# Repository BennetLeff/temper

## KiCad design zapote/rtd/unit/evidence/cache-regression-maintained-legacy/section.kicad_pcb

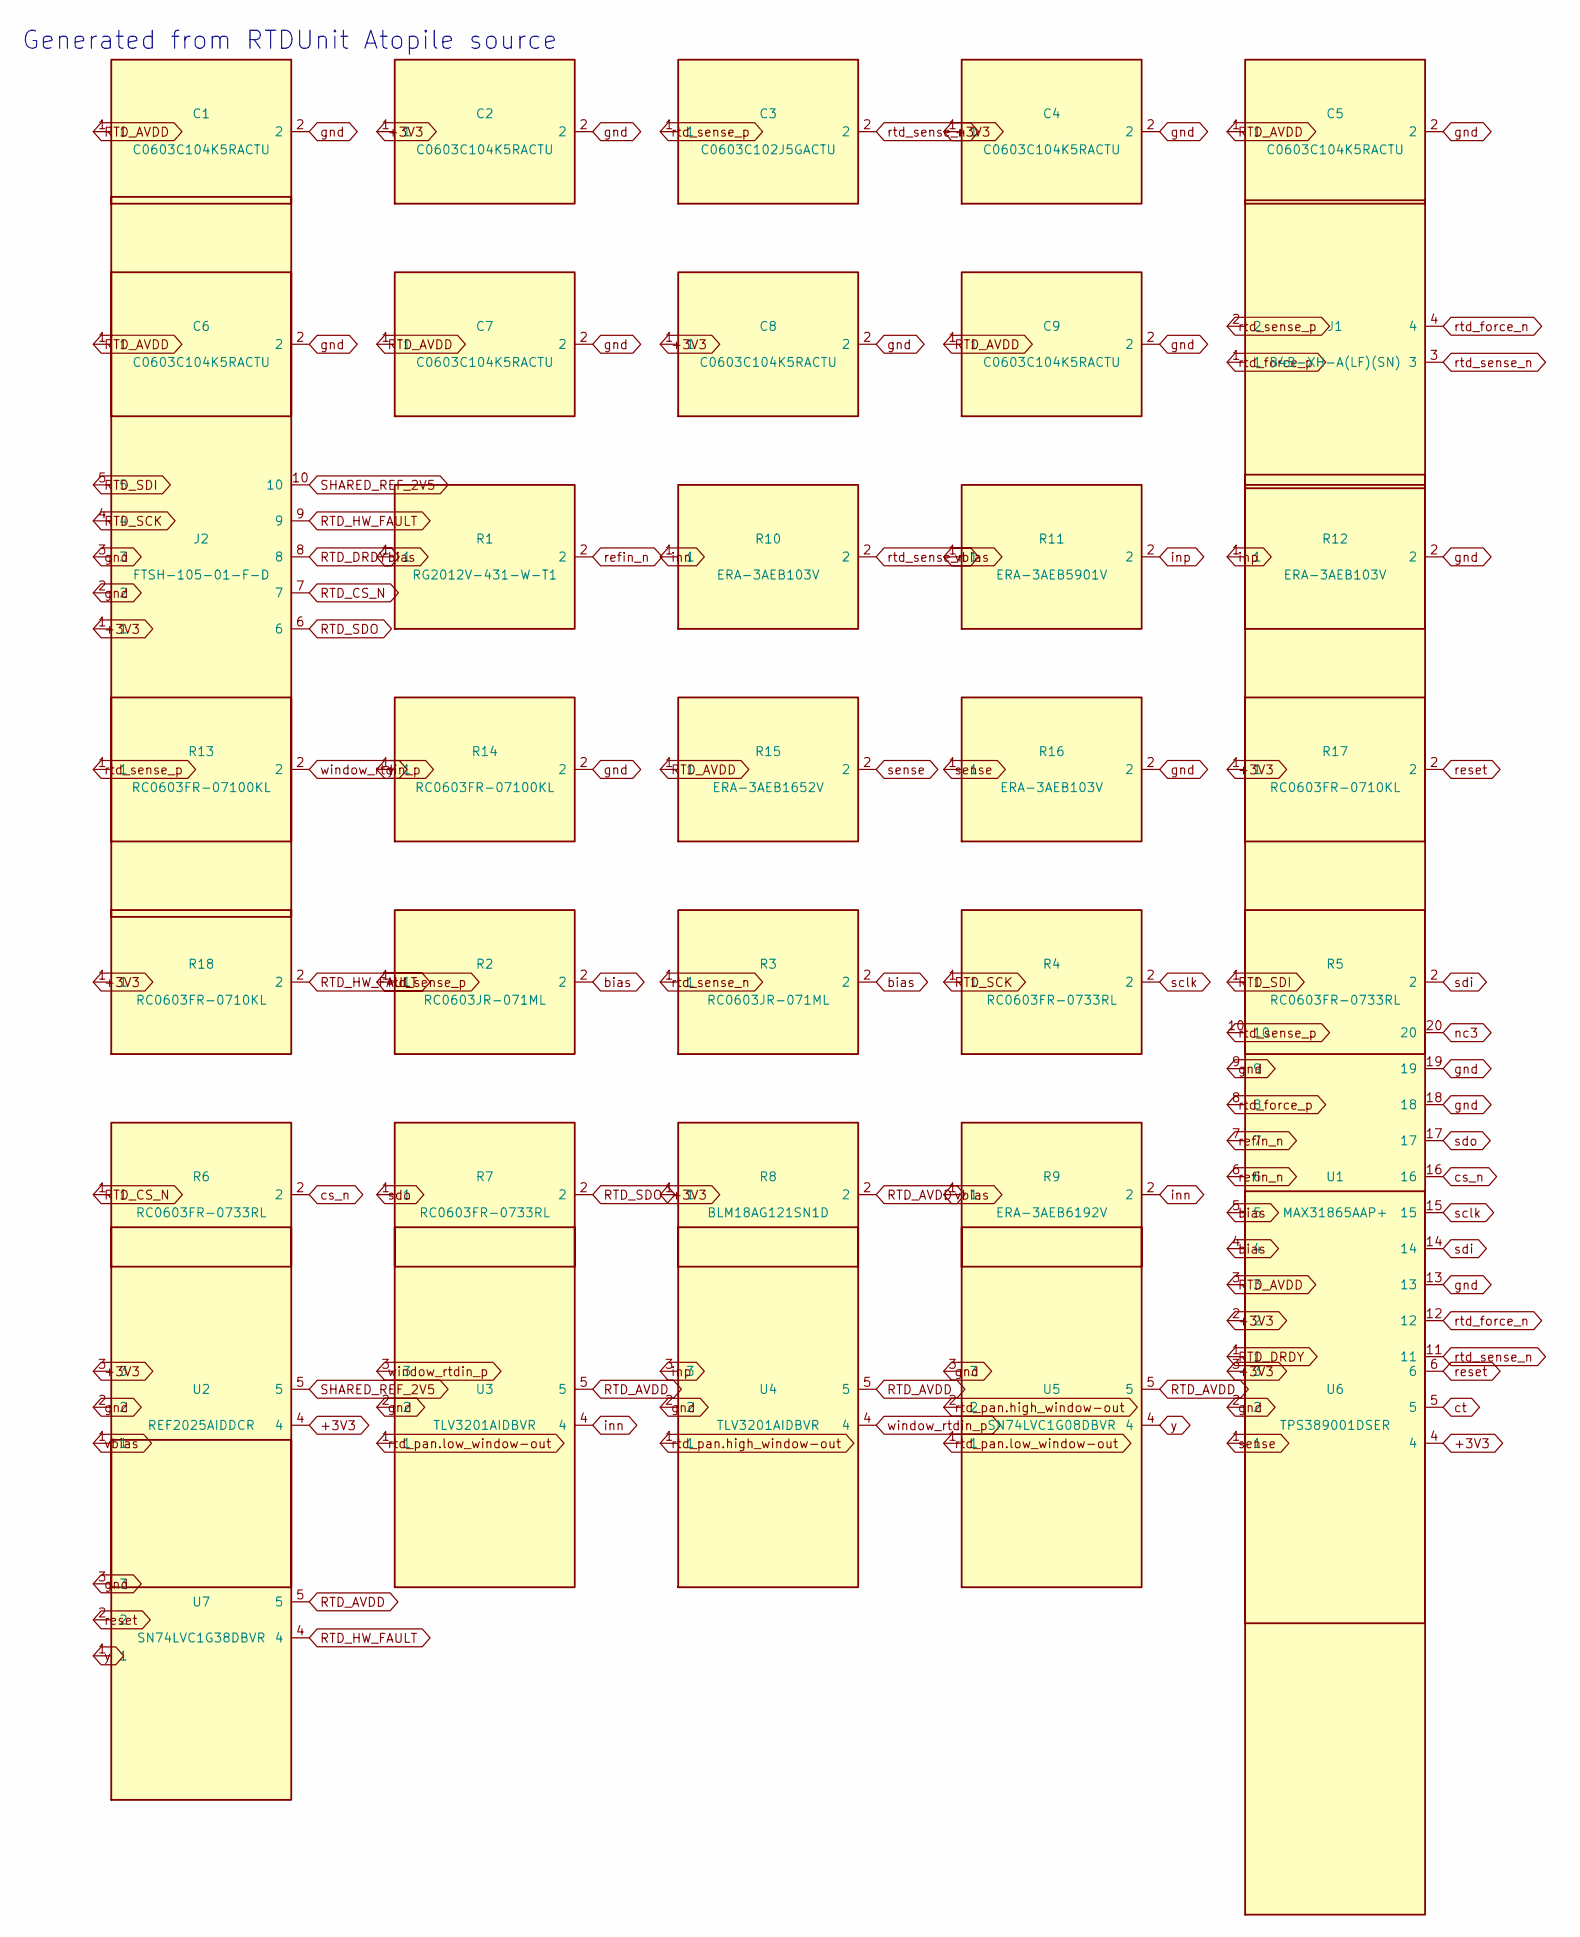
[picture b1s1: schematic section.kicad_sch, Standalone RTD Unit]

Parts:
C1, C2, C4, C5, C6, C7, C8, C9: C0603C104K5RACTU; C_0603_1608Metric
C3: C0603C102J5GACTU; C_0603_1608Metric
J1: B4B-XH-A(LF)(SN); JST_XH_B4B-XH-A_1x04_P2.50mm_Vertical
J2: FTSH-105-01-F-D; FTSH-105-01-F-D_2x5_P1.27mm
R1: RG2012V-431-W-T1; R_0805_2012Metric
R2, R3: RC0603JR-071ML; R_0603_1608Metric
R4, R5, R6, R7: RC0603FR-0733RL; R_0603_1608Metric
R8: BLM18AG121SN1D; L_0603_1608Metric
R9: ERA-3AEB6192V; R_0603_1608Metric
R10, R12, R16: ERA-3AEB103V; R_0603_1608Metric
R11: ERA-3AEB5901V; R_0603_1608Metric
R13, R14: RC0603FR-07100KL; R_0603_1608Metric
R15: ERA-3AEB1652V; R_0603_1608Metric
R17, R18: RC0603FR-0710KL; R_0603_1608Metric
U1: MAX31865AAP+; SSOP-20_3.9x8.7mm_P0.635mm
U2: REF2025AIDDCR; SOT-23-5
U3, U4: TLV3201AIDBVR; SOT-23-5
U5: SN74LVC1G08DBVR; SOT-23-5
U6: TPS389001DSER; TPS389001DSER_WSON-6_DSE
U7: SN74LVC1G38DBVR; SOT-23-5

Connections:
+3V3: C2.1, C4.1, C8.1, J2.1, R8.1, R17.1, R18.1, U1.2, U2.3, U2.4, U6.3, U6.4
RTD_AVDD: C1.1, C5.1, C6.1, C7.1, C9.1, R8.2, R15.1, U1.3, U3.5, U4.5, U5.5, U7.5
RTD_CS_N: J2.7, R6.1
RTD_DRDY: J2.8, U1.1
RTD_HW_FAULT: J2.9, R18.2, U7.4
RTD_SCK: J2.4, R4.1
RTD_SDI: J2.5, R5.1
RTD_SDO: J2.6, R7.2
SHARED_REF_2V5: J2.10, U2.5
bias: R1.1, R2.2, R3.2, U1.4, U1.5
cs_n: R6.2, U1.16
ct: U6.5
gnd: C1.2, C2.2, C4.2, C5.2, C6.2, C7.2, C8.2, C9.2, J2.2, J2.3, R12.2, R14.2, R16.2, U1.9, U1.13, U1.18, U1.19, U2.2, U3.2, U4.2, U5.3, U6.2, U7.3
inn: R9.2, R10.1, U3.4
inp: R11.2, R12.1, U4.3
nc3: U1.20
refin_n: R1.2, U1.6, U1.7
reset: R17.2, U6.6, U7.2
rtd_force_n: J1.4, U1.12
rtd_force_p: J1.1, U1.8
rtd_pan.high_window-out: U4.1, U5.2
rtd_pan.low_window-out: U3.1, U5.1
rtd_sense_n: C3.2, J1.3, R3.1, R10.2, U1.11
rtd_sense_p: C3.1, J1.2, R2.1, R13.1, U1.10
sclk: R4.2, U1.15
sdi: R5.2, U1.14
sdo: R7.1, U1.17
sense: R15.2, R16.1, U6.1
vbias: R9.1, R11.1, U2.1
window_rtdin_p: R13.2, U3.3, U4.4
y: R14.1, U5.4, U7.1

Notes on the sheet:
Generated from RTDUnit Atopile source

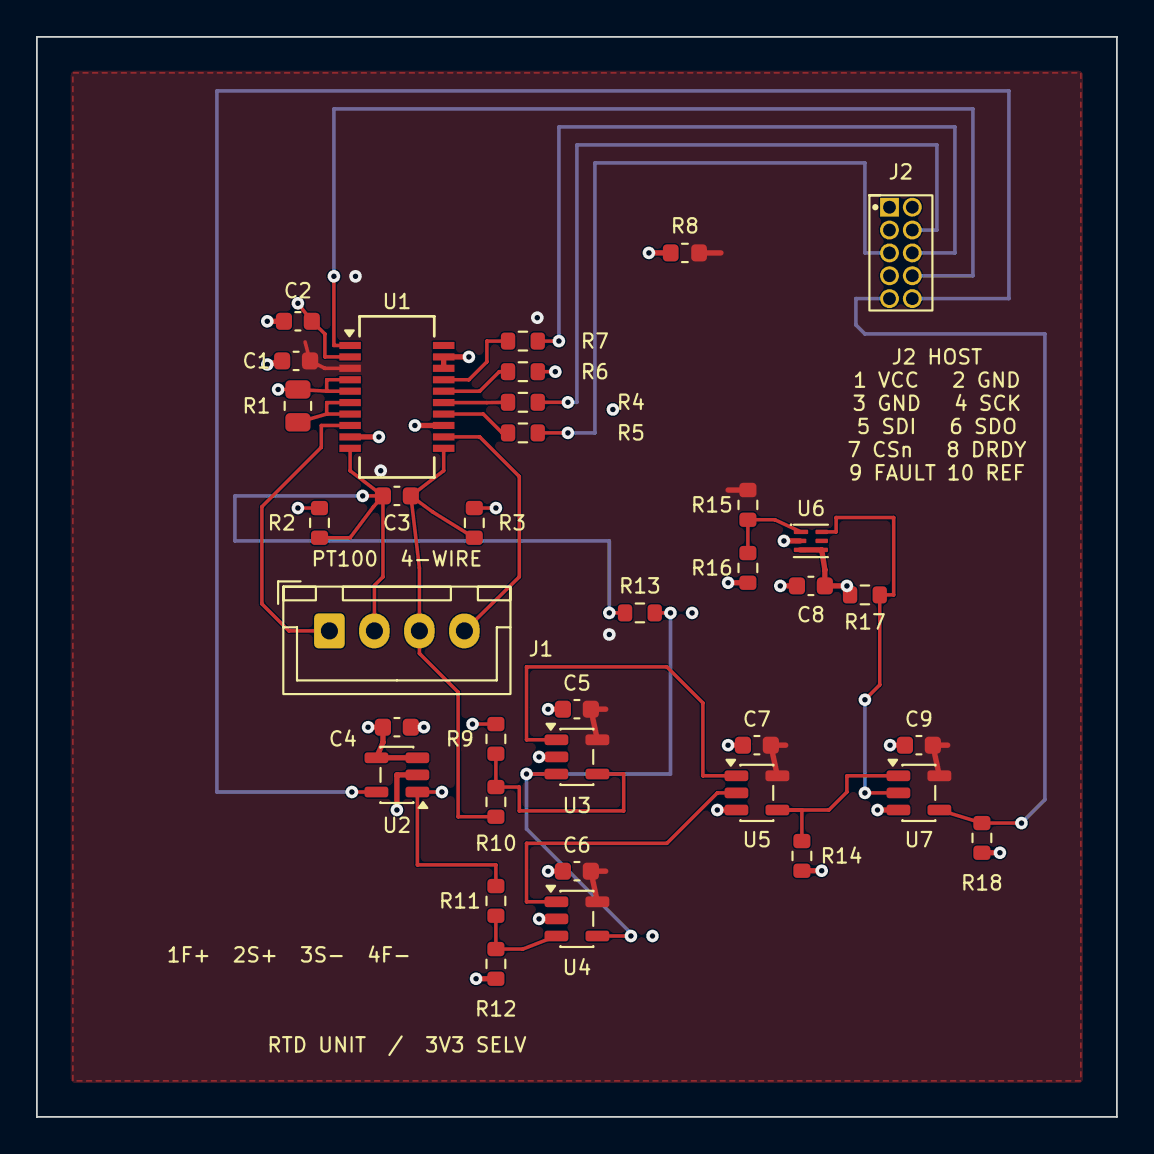
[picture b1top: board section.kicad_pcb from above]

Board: 4 copper layers, 60.0 x 60.0 mm, 36 parts (0 on the bottom side), 29 nets.

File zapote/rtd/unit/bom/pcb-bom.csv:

Quantity,References,Manufacturer part number,Value,Footprint,Source instances
1,J1,B4B-XH-A(LF)(SN),,Connector_JST:JST_XH_B4B-XH-A_1x04_P2.50mm_Vertical,rtd_pan.j_rtd1
1,R8,BLM18AG121SN1D,120ohm,Inductor_SMD:L_0603_1608Metric,rtd_pan.fb_power
1,C3,C0603C102J5GACTU,1nF,Capacitor_SMD:C_0603_1608Metric,rtd_pan.c_rtd_input
8,C1 C2 C4 C5 C6 C7 C8 C9,C0603C104K5RACTU,100nF,Capacitor_SMD:C_0603_1608Metric,rtd_pan.c_vdd rtd_pan.c_dvdd rtd_pan.c_reference rtd_pan.c_low_window rtd_pan.c_high_window rtd_pan.c_window_and rtd_pan.c_rail_monitor rtd_pan.c_fault_nand
3,R10 R12 R16,ERA-3AEB103V,10kohm +/- 0.1%,Resistor_SMD:R_0603_1608Metric,rtd_pan.r_low_bottom rtd_pan.r_high_bottom rtd_pan.r_avdd_bottom
1,R15,ERA-3AEB1652V,16.5kohm +/- 0.1%,Resistor_SMD:R_0603_1608Metric,rtd_pan.r_avdd_top
1,R11,ERA-3AEB5901V,5.9kohm +/- 0.1%,Resistor_SMD:R_0603_1608Metric,rtd_pan.r_high_top
1,R9,ERA-3AEB6192V,61.9kohm +/- 0.1%,Resistor_SMD:R_0603_1608Metric,rtd_pan.r_low_top
1,J2,FTSH-105-01-F-D,,Temper_RTD:FTSH-105-01-F-D_2x5_P1.27mm,unit_io
1,U1,MAX31865AAP+,,Package_SO:SSOP-20_3.9x8.7mm_P0.635mm,rtd_pan.adc
2,R13 R14,RC0603FR-07100KL,100kohm +/- 1%,Resistor_SMD:R_0603_1608Metric,rtd_pan.r_window_sense_p rtd_pan.r_window_ok_pulldown
2,R17 R18,RC0603FR-0710KL,10kohm +/- 1%,Resistor_SMD:R_0603_1608Metric,rtd_pan.r_rail_ok_pullup rtd_pan.r_fault_pullup
4,R4 R5 R6 R7,RC0603FR-0733RL,33ohm +/- 1%,Resistor_SMD:R_0603_1608Metric,rtd_pan.r_sclk rtd_pan.r_mosi rtd_pan.r_cs rtd_pan.r_miso
2,R2 R3,RC0603JR-071ML,1Mohm +/- 5%,Resistor_SMD:R_0603_1608Metric,rtd_pan.r_rtdin_p_bias rtd_pan.r_rtdin_n_bias
1,U2,REF2025AIDDCR,,Package_TO_SOT_SMD:SOT-23-5,rtd_pan.reference
1,R1,RG2012V-431-W-T1,430ohm +/- 0.05%,Resistor_SMD:R_0805_2012Metric,rtd_pan.r_ref
1,U5,SN74LVC1G08DBVR,,Package_TO_SOT_SMD:SOT-23-5,rtd_pan.window_and
1,U7,SN74LVC1G38DBVR,,Package_TO_SOT_SMD:SOT-23-5,rtd_pan.fault_nand
2,U3 U4,TLV3201AIDBVR,,Package_TO_SOT_SMD:SOT-23-5,rtd_pan.low_window rtd_pan.high_window
1,U6,TPS389001DSER,,Temper_RTD:TPS389001DSER_WSON-6_DSE,rtd_pan.rail_monitor
